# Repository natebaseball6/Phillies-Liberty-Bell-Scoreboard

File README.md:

# Phillies-Liberty-Bell-Scoreboard

Description: 

This project is intended to act as a desk toy resembling the Citizens' Bank Park Liberty Bell that "rings" whenever the Phillies hit a home run or win a game. The "bell" will feature a scoreboard on the front that accurately displays the live score, count, outs, inning, and more of a game.

The entire construction will be comprised of circuit board to minimize cost, as many small scale services such as JLC-PCB offer a fixed price for certain sizes of board, even if they are cut to smaller or more unique shapes. The shape of the bell will be one large circuit board, and the stand that holds it up will be a combination of smaller ones. 

The circuit will be ESP32 based, and overall very rudimentary and simple. Seven segment displays, individual LEDs, and a buzzer will be addressed by this ESP32.

The ESP32 will be connected to the local Wi-Fi network, and will fetch data from the MLB API for live scores.

Current Progress:

Brainstorming: DONE

Schematic Design (KiCAD): DONE

PCB Design (KiCAD): DONE

Physical Construction (JLCPCB + Digi Key): INCOMPLETE

Initial Test: INCOMPLETE

Programming: INCOMPLETE

API Test: INCOMPLETE

Polishing/Completion: INCOMPLETE

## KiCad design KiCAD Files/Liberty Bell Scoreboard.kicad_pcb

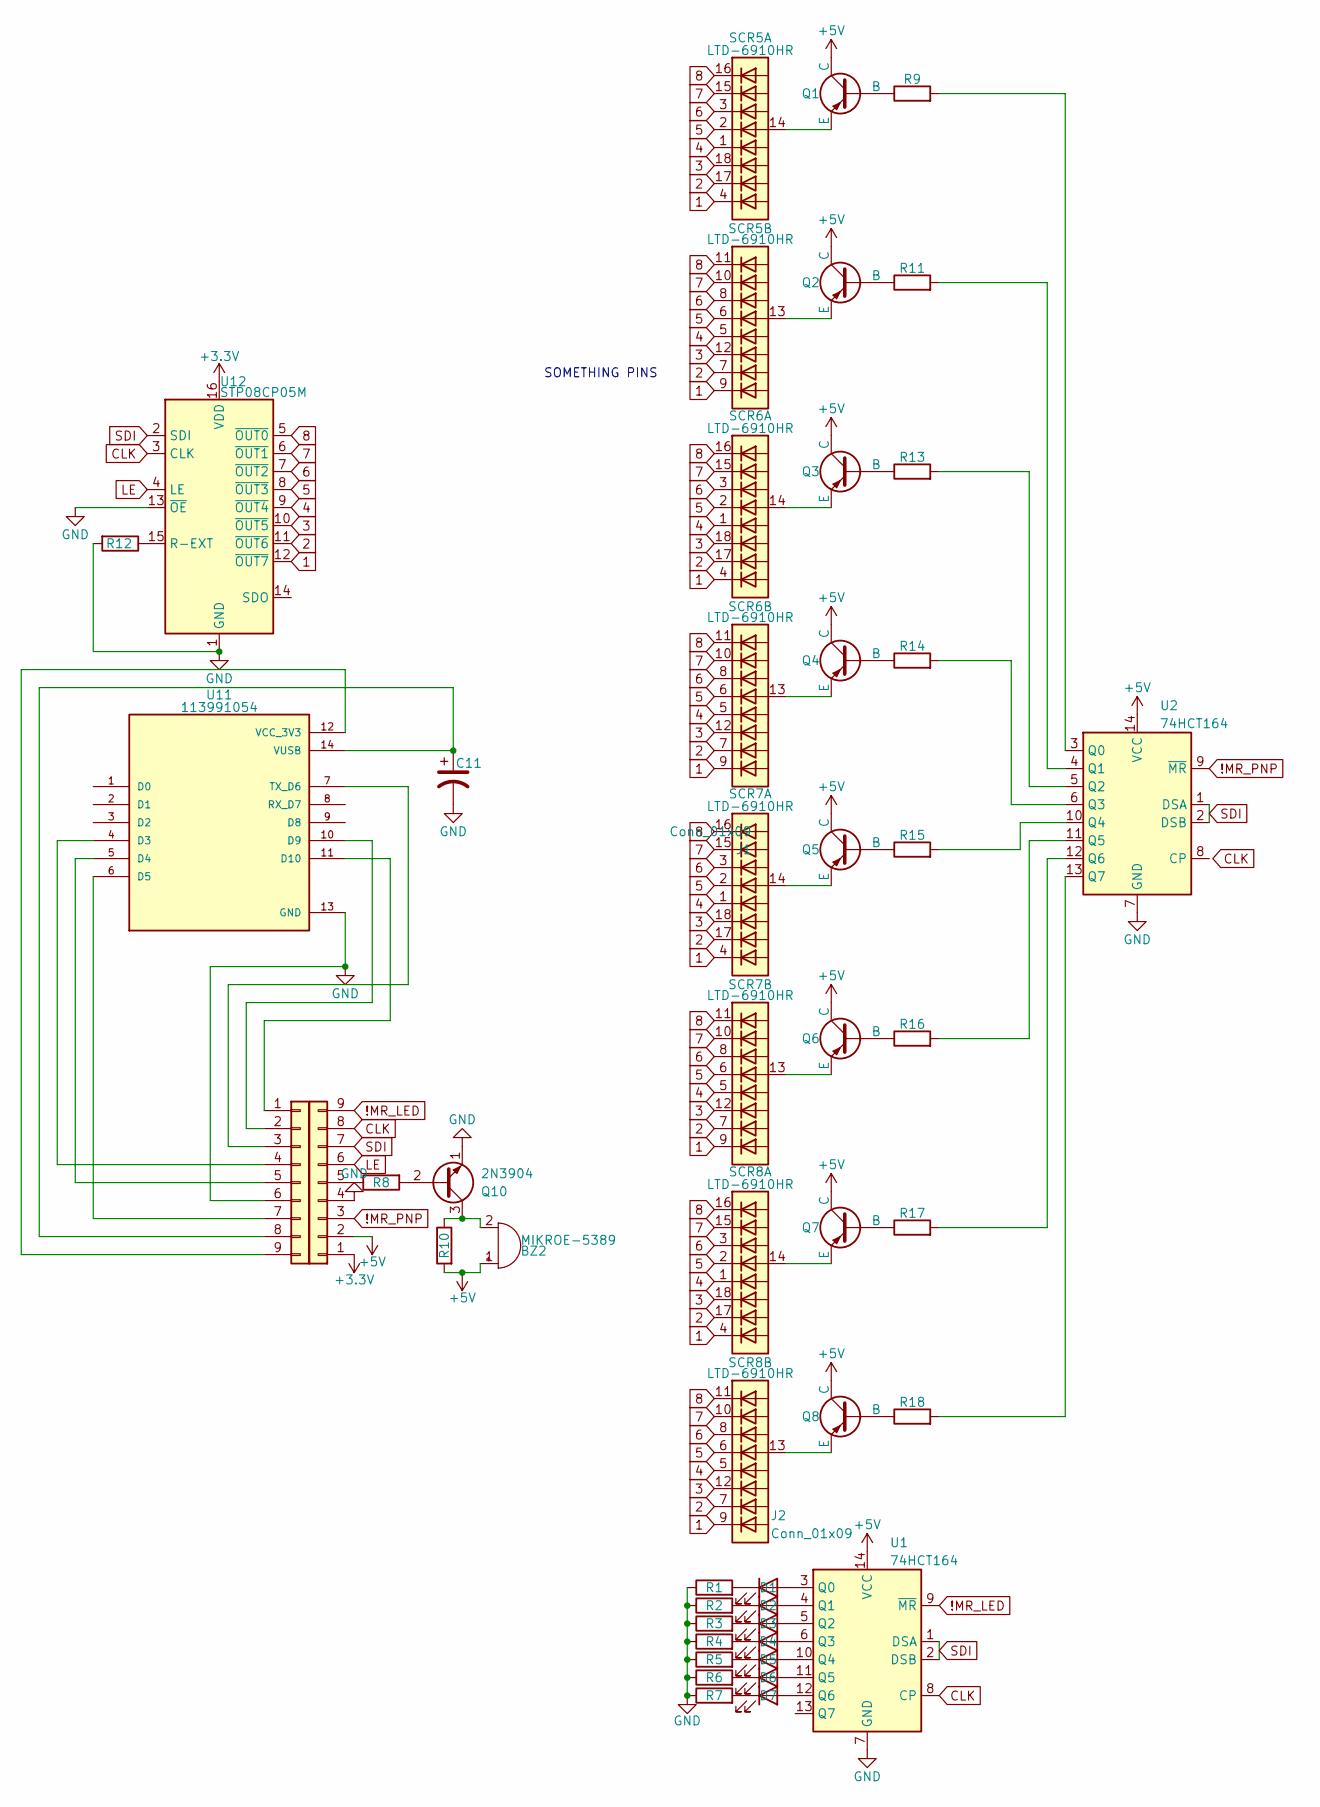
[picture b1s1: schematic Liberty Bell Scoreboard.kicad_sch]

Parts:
BZ2: MIKROE-5389; LS_CT30P_CGE
C11: UCD1C101MCL1GS; CP_Elec_6.3x5.9
D1, D2, D3, D4, D5, D6, D7: SML-D12U1WT86; LED_0603_1608Metric_Pad1.05x0.95mm_HandSolder
J1: Conn_01x09; PinSocket_1x09_P2.54mm_Vertical
J2: Conn_01x09; PinHeader_1x09_P2.54mm_Horizontal
Q1, Q2, Q3, Q4, Q5, Q6, Q7, Q8: MMBT3906-7-F-W; SOT-23_Handsoldering
Q10: 2N3904; TO-92_Inline
R1, R2, R3, R4, R5, R6, R7: RNCP1206FTD150R; R_1206_3216Metric_Pad1.30x1.75mm_HandSolder
R8, R9, R10, R11, R13, R14, R15, R16, R17, R18: RK73H2ATTD1001F; R_0805_2012Metric_Pad1.20x1.40mm_HandSolder
R12: RMCF1206JT240R; R_1206_3216Metric_Pad1.30x1.75mm_HandSolder
SCR5, SCR6, SCR7, SCR8: LTD-6910HR; HDSP-4830
U1, U2: 74HCT164; SOIC-14_3.9x8.7mm_P1.27mm
U11: 113991054; MODULE_113991054; PARTREV 23/05/2022; DigiKey_Part_Number 1597-113991054-ND
U12: STP08CP05M; SOIC-16_3.9x9.9mm_P1.27mm

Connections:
1: SCR5.4 (A), SCR5.9 (A), SCR6.4 (A), SCR6.9 (A), SCR7.4 (A), SCR7.9 (A), SCR8.4 (A), SCR8.9 (A), U12.12 (~OUT7)
2: SCR5.7 (A), SCR5.17 (A), SCR6.7 (A), SCR6.17 (A), SCR7.7 (A), SCR7.17 (A), SCR8.7 (A), SCR8.17 (A), U12.11 (~OUT6)
3: SCR5.12, SCR5.18 (12), SCR6.12, SCR6.18 (12), SCR7.12, SCR7.18 (12), SCR8.12, SCR8.18 (12), U12.10 (~OUT5)
4: SCR5.1 (A), SCR5.5 (A), SCR6.1 (A), SCR6.5 (A), SCR7.1 (A), SCR7.5 (A), SCR8.1 (A), SCR8.5 (A), U12.9 (~OUT4)
5: SCR5.2, SCR5.6 (A), SCR6.2, SCR6.6 (A), SCR7.2, SCR7.6 (A), SCR8.2, SCR8.6 (A), U12.8 (~OUT3)
6: SCR5.3, SCR5.8 (A), SCR6.3, SCR6.8 (A), SCR7.3, SCR7.8 (A), SCR8.3, SCR8.8 (A), U12.7 (~OUT2)
7: SCR5.10 (0), SCR5.15 (0), SCR6.10 (0), SCR6.15 (0), SCR7.10 (0), SCR7.15 (0), SCR8.10 (0), SCR8.15 (0), U12.6 (~OUT1)
8: SCR5.11 (A), SCR5.16 (A), SCR6.11 (A), SCR6.16 (A), SCR7.11 (A), SCR7.16 (A), SCR8.11 (A), SCR8.16 (A), U12.5 (~OUT0)
!MR_LED: J1.9, U1.9 (~MR)
!MR_PNP: J1.3, U2.9 (~MR)
+3.3V: J1.1, U12.16 (VDD)
+5V: BZ2.1 (+), J1.2, Q1.1 (C), Q2.1 (C), Q3.1 (C), Q4.1 (C), Q5.1 (C), Q6.1 (C), Q7.1 (C), Q8.1 (C), R10.2, U1.14 (VCC), U2.14 (VCC)
CLK: J1.8, U1.8 (CP), U12.3 (CLK)
GND: C11.2, J1.4, J2.6, Q10.1 (E), R1.1, R2.1, R3.1, R4.1, R5.1, R6.1, R7.1, R12.2, U1.7 (GND), U2.7 (GND), U11.13 (GND), U12.1 (GND), U12.13 (~OE)
LE: J1.6, U12.4 (LE)
unnamed: BZ2.2 (-), Q10.3 (C), R10.1
unnamed: D1.2 (A), U1.3 (Q0)
unnamed: D1.1 (K), R1.2
unnamed: D2.2 (A), U1.4 (Q1)
unnamed: D2.1 (K), R2.2
unnamed: D3.2 (A), U1.5 (Q2)
unnamed: D3.1 (K), R3.2
unnamed: D4.2 (A), U1.6 (Q3)
unnamed: D4.1 (K), R4.2
unnamed: D5.2 (A), U1.10 (Q4)
unnamed: D5.1 (K), R5.2
unnamed: D6.2 (A), U1.11 (Q5)
unnamed: D6.1 (K), R6.2
unnamed: D7.2 (A), U1.12 (Q6)
unnamed: D7.1 (K), R7.2
unnamed: J1.5, R8.1
unnamed: J2.1, U11.11 (D10)
unnamed: J2.2, U11.10 (D9)
unnamed: J2.3, U11.7 (TX_D6)
unnamed: J2.4, U11.4 (D3)
unnamed: J2.5, U11.5 (D4)
unnamed: J2.7, U11.6 (D5)
unnamed: C11.1, J2.8, U11.14 (VUSB)
unnamed: J2.9, U11.12 (VCC_3V3)
unnamed: Q1.2 (B), R9.1
unnamed: Q1.3 (E), SCR5.14 (DIGIT_2)
unnamed: Q2.2 (B), R11.1
unnamed: Q2.3 (E), SCR5.13 (DIGIT_2)
unnamed: Q3.2 (B), R13.1
unnamed: Q3.3 (E), SCR6.14 (DIGIT_2)
unnamed: Q4.2 (B), R14.1
unnamed: Q4.3 (E), SCR6.13 (DIGIT_2)
unnamed: Q5.2 (B), R15.1
unnamed: Q5.3 (E), SCR7.14 (DIGIT_2)
unnamed: Q6.2 (B), R16.1
unnamed: Q6.3 (E), SCR7.13 (DIGIT_2)
unnamed: Q7.2 (B), R17.1
unnamed: Q7.3 (E), SCR8.14 (DIGIT_2)
unnamed: Q8.2 (B), R18.1
unnamed: Q8.3 (E), SCR8.13 (DIGIT_2)
unnamed: Q10.2 (B), R8.2
unnamed: R9.2, U2.3 (Q0)
unnamed: R11.2, U2.4 (Q1)
unnamed: R13.2, U2.5 (Q2)
unnamed: R14.2, U2.6 (Q3)
unnamed: R15.2, U2.10 (Q4)
unnamed: R16.2, U2.11 (Q5)
unnamed: R17.2, U2.12 (Q6)
unnamed: R18.2, U2.13 (Q7)
unnamed: R12.1, U12.15 (R-EXT)
SDI: J1.7, U1.1 (DSA), U1.2 (DSB), U2.1 (DSA), U2.2 (DSB), U12.2 (SDI)

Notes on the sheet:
SOMETHING PINS

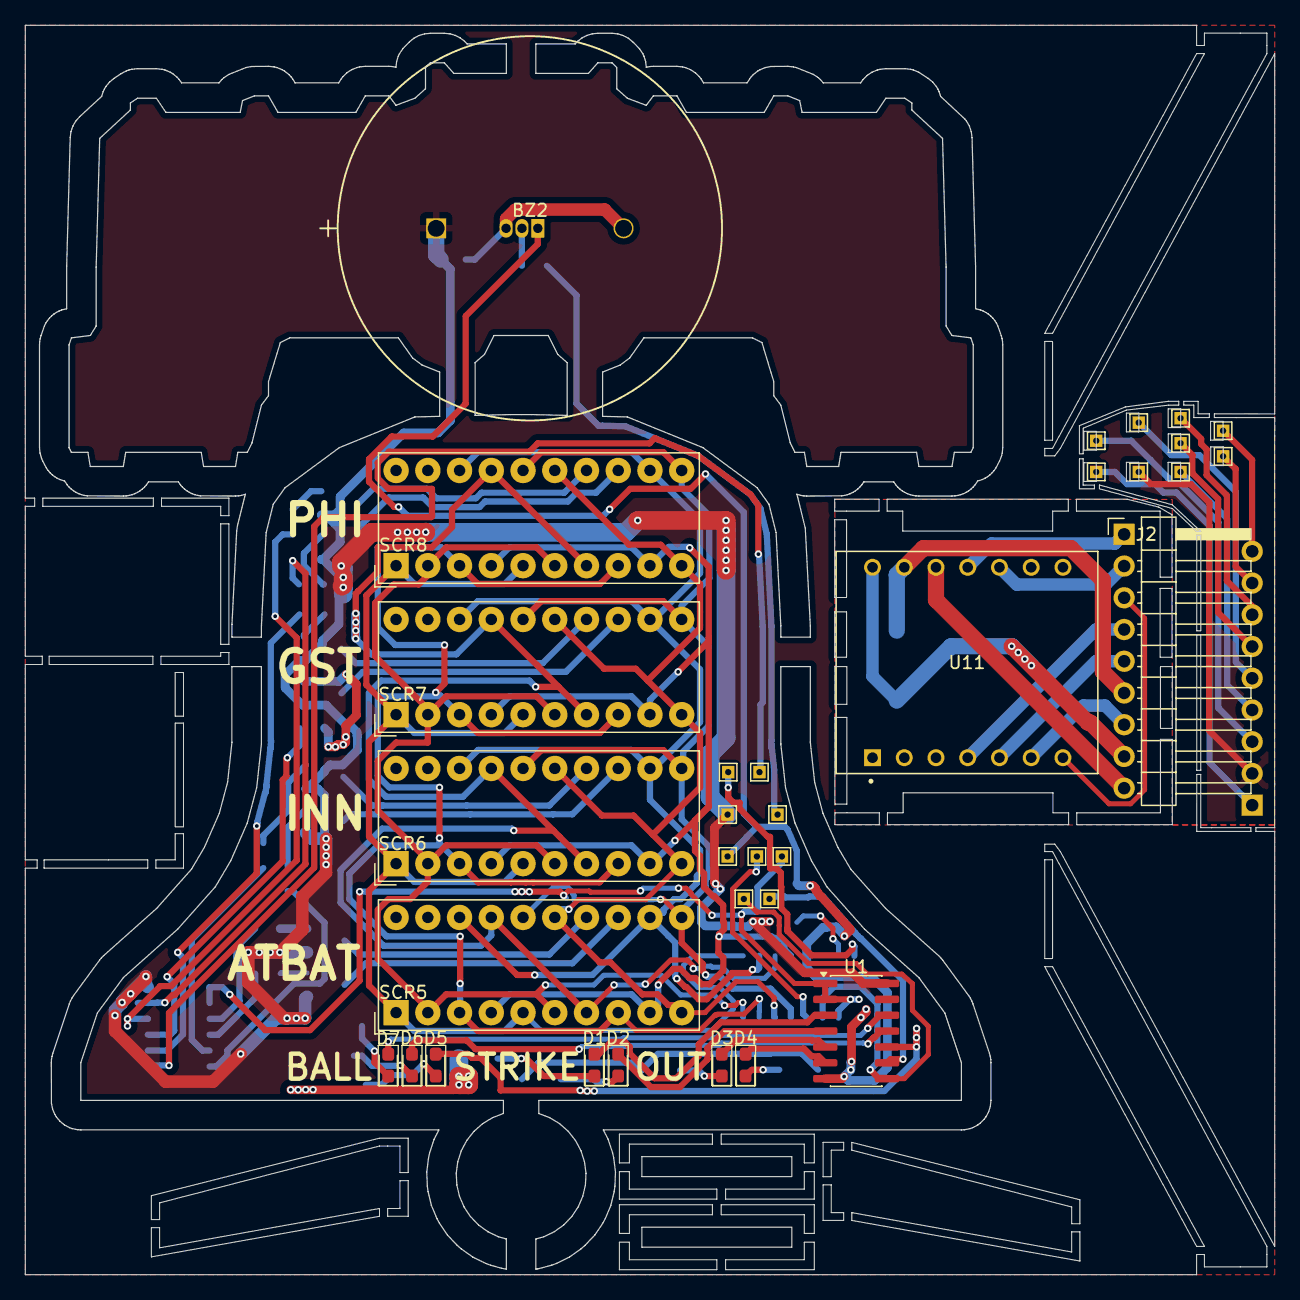
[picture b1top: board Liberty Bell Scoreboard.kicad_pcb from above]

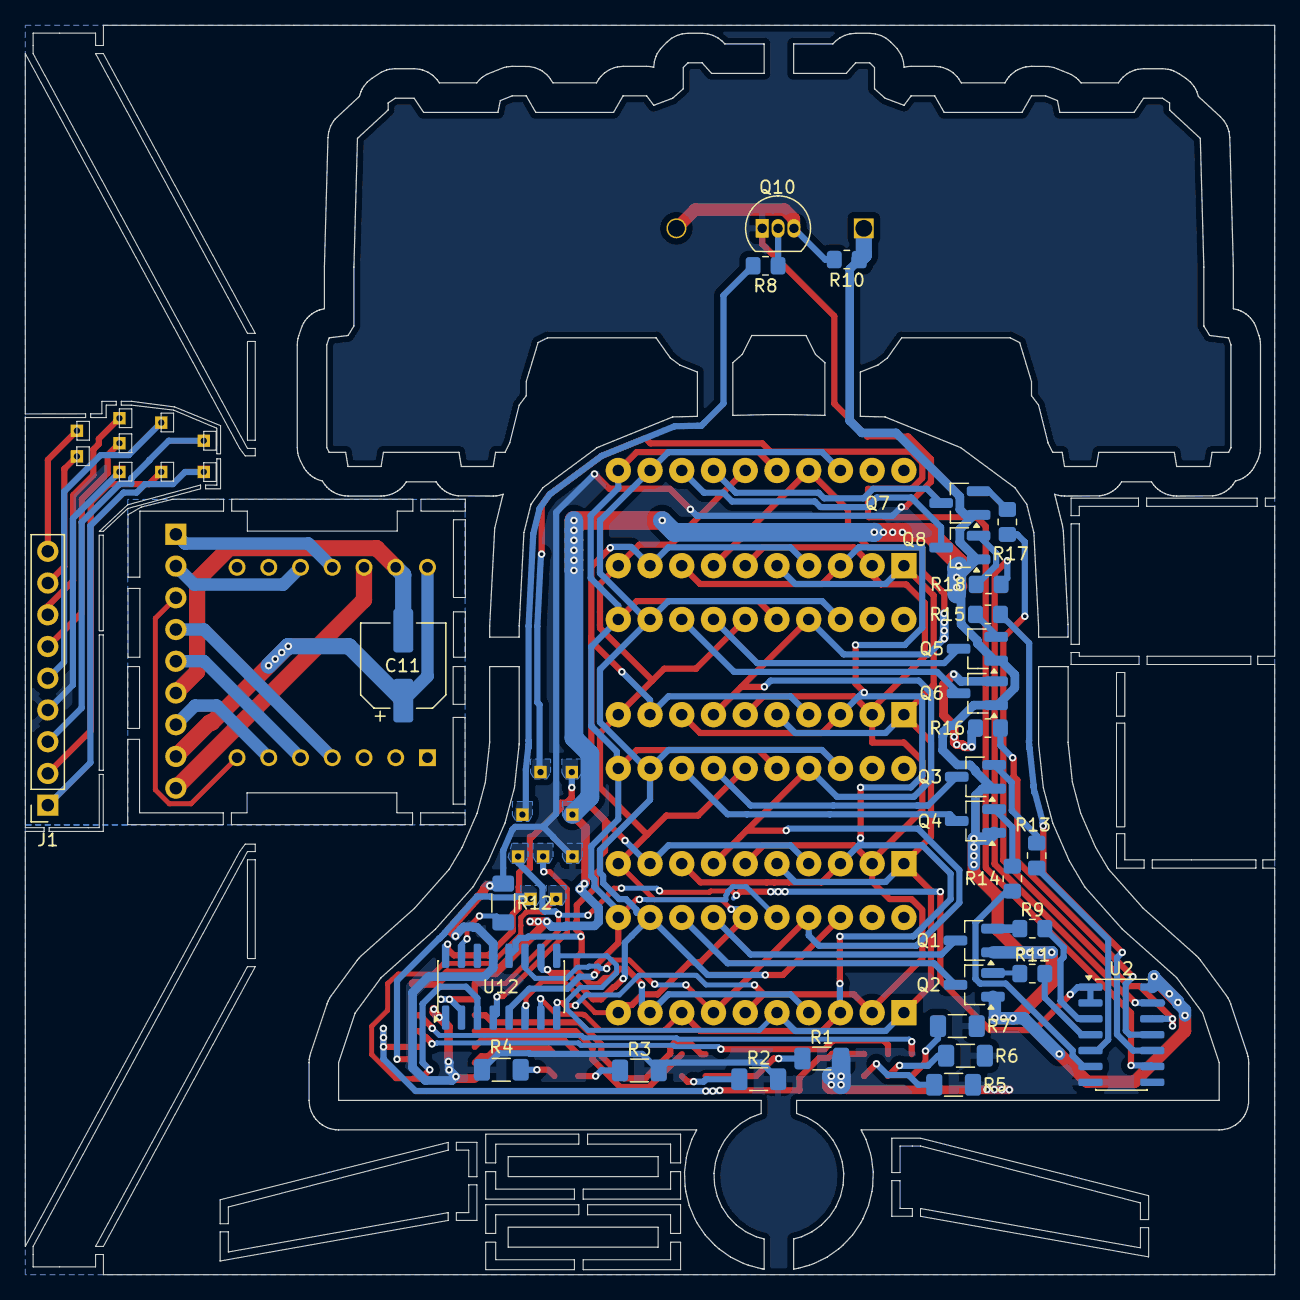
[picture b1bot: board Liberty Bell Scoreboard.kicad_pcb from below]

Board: 2 copper layers, 100.0 x 99.9 mm, 46 parts (31 on the bottom side), 66 nets.

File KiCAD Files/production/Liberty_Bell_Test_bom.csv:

Designator,Footprint,Quantity,Value,LCSC Part #
BZ2,LS_CT30P_CGE,1,MIKROE-5389,
C11,CP_Elec_6.3x5.9,1,UCD1C101MCL1GS,
"D1, D2, D3, D4, D5, D6, D7",0603,7,SML-D12U1WT86,
J1,PinSocket_1x09_P2.54mm_Vertical,1,Conn_01x09,
J2,PinHeader_1x09_P2.54mm_Horizontal,1,Conn_01x09,
"Q1, Q2, Q3, Q4, Q5, Q6, Q7, Q8",SOT-23_Handsoldering,8,MMBT3906-7-F-W,
Q10,TO-92_Inline,1,2N3904,
"R1, R2, R3, R4, R5, R6, R7",1206,7,RNCP1206FTD150R,
"R10, R11, R13, R14, R15, R16, R17, R18, R8, R9",0805,10,RK73H2ATTD1001F,
R12,1206,1,RMCF1206JT240R,
"SCR5, SCR6, SCR7, SCR8",HDSP-4830,4,LTD-6910HR,
"U1, U2",SOIC-14_3.9x8.7mm_P1.27mm,2,74HCT164,
U11,MODULE_113991054,1,113991054,
U12,SOIC-16_3.9x9.9mm_P1.27mm,1,STP08CP05M,

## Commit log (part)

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2026-02-10 Create Soemt
